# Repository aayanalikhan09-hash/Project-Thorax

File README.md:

# Project-Thorax
My first attempt at a custom PCB used to enable the detection of microplastics in different bodies of water tested across many different kinds of water.

This is a unique project state, so I will explain it.
Below is my ship comment that I feel explains the status well:

Hello everyone!
This is my magnum opus --- unfinished.
I hope to finish it soon and ship it to a different YSWS for funding, but for now it is just a concept in software.

I will still explain it, however.

This is meant to be a microplastic detection PCB that uses light spectroscopy to determine whether microplastics are present in water based on machine learning.

I wanted to make the PCB myself to learn the basics of electrical engineering and to also have some design freedom when it came to using specific components. The design was meant to use the very powerful ATSAMD series chip to coordinate many different concurrent processes, such as data transfer, flash memory storage, SD card storage, live ML model usage, Bluetooth data transfer, and data collection using the integrated sensor.

My data-collection plan is to set up a controlled lab environment with a single light source on the board, then take microplastic samples and place them in distilled water. After this, I will conduct hundreds of trials and collect data to see how the light response is received by the sensor. Each material's light response or reflected wavelength will allow the ML model to understand what constitutes a plastic/specifically red plastic, and what is not. The goal is to keep the project and its dependent variables as simple as possible so as not to overcomplicate data analysis and manipulation.

Post data collection, I plan to use the data to train a basic machine learning model on the patterns of how light is reflected on specific materials. This will allow for the distinction between specific material types and complete the project's overall goal of detecting microplastics in water. I intend to refine this later on with more funding and resources available to make this a reality and a golden standard to determine microplastic content in water.

For now, this is goodbye, everyone. It was fun seeing all of your amazing projects, and now you will see mine :)

See you guys soon!

Now that you have read through that, I must explain why a demo wasn't possible, what I'm doing in place of that, and how to get this thing running.

A demo was not possible because I've been bombarded with homework. If I had even had 75 percent of the homework I have right now, this project would likely be complete, amongst many other things. For reference, I'm taking 4 APs, two dual enrollments, organizing a haven(haven.hackclub.com/philly - GO CHECK IT OUT AHHH), youth group lead, library Teen Advisory Board president, and much more I'm probably forgetting. It's self-inflicted, so I have nobody to blame but myself, but that's an explanation, not an excuse.

What I'm doing is making the project files public, because that's literally all I have. I wish I could say I had more, but I don't. There is literally nothing else for me to give to all of you. I wish I could at least give the PCB, but then at that point I could ship, so it is what it is.

If you wanted to get this running, you can place TVS diodes on all the likely-to-be-exposed components and finish the PCB yourself in the PCB editor. A lot of the actual connections have all been done properly based on schematics; it just needs electrostatic discharge protection, so that's why I'm using TVS diodes. Technically, this is good to go right now, but you will absolutely static shock the components and fry them.

Until I figure out TVS diodes, I will be unable to properly ship this project. So I hope to figure that out soon and let you guys know how that goes!
I have attached a build notes document for your potential amusement; it's not all that exciting, but it does have some notes that I made for myself while making the PCB.
https://docs.google.com/document/d/10ZuE0ZeMz8bDbDXp7TKcbCHwWacSMxAw3u6ysEummEY/edit?usp=sharing

This is the end for now, but I will be back to finish this; I promise.

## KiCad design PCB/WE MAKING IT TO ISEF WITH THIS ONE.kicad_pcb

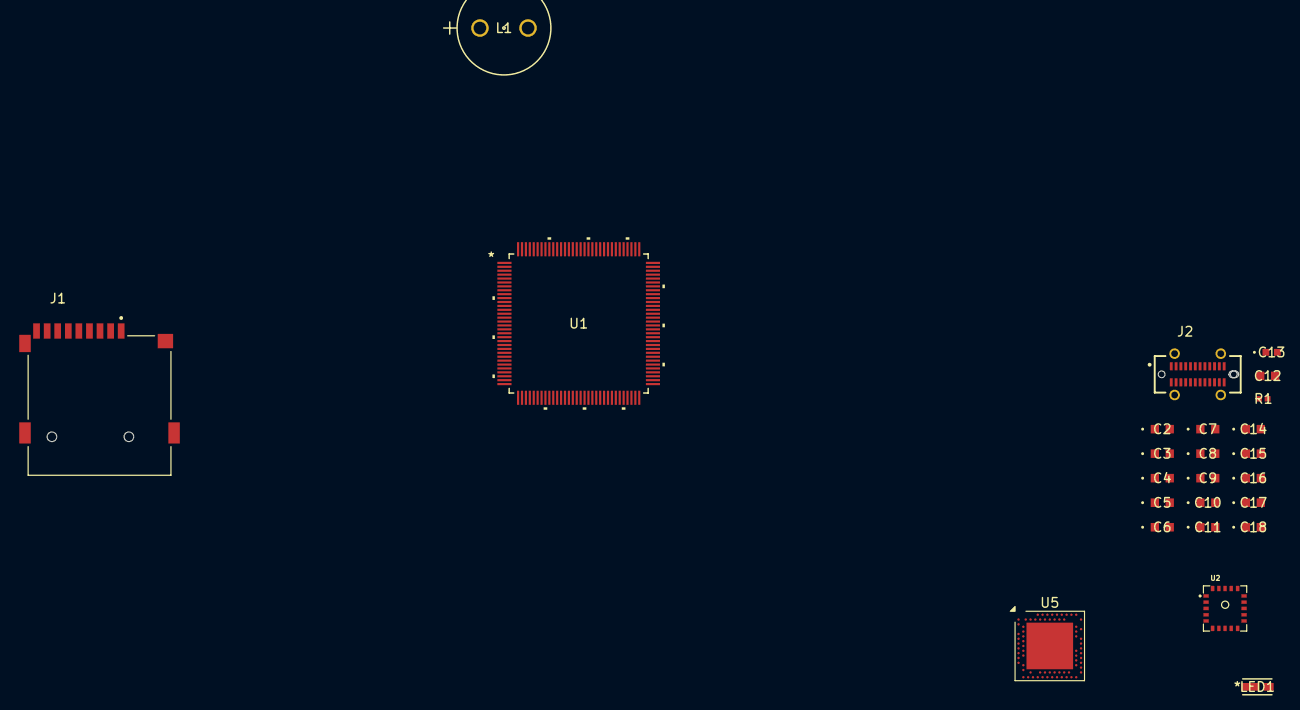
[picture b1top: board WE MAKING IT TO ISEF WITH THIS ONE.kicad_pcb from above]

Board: 2 copper layers, 25 parts (0 on the bottom side), 12 nets, no tracks yet.

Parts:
C2, C3, C4, C5, C6, C7, C8, C9, C10, C11, C14, C15, C16, C17, C18: C_US; CAP_GCM18_1p7X0p9X0p9_MUR
C12: C_US; CAP_GXT_1p7x0p9x0p9_MUR
C13: C_US; CAP_G_M1502_MUR
J1: MSD-1-A - SD Card Read; CUI_MSD-1-A
J2: USB_C_Receptacle; GCT_USB4225-03-1000-C_REVA
L1: L; 1300R_MUR
LED1: L130-5780HE1400001 - LED; LED_L130-5780HE1400001_PLL
R1: R; STA_RMCF0402_STP
U1: ATSAMD51P20A-AUT; TQFP128_14X14MC_MCH
U2: AS7263-BLGT - Spectrometer; PQFN065P470X450X260-20N
U5: nRF52833_QIxx; Nordic_AQFN-73-1EP_7x7mm_P0.5mm

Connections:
+3.3V: C2.1, C3.1, C4.1, C5.1, C6.1, C7.1, C8.1, C9.1, C10.1, C11.1, C15.1, C16.1, C17.1, R1.1, U1.6 (VDDANA), U1.15 (VDDANA), U1.26 (VDDANA), U1.32 (VDDIOB), U1.37 (VDDIOB), U1.46 (VDDIO), U1.54 (VDDIO), U1.65 (VDDIO), U1.79 (VDDIO), U1.91 (VDDIO), U1.97 (VDDIO), U1.107 (VDDIO), U1.118 (VDDIO)
GND: J1.G1 (COVER_GND), J1.G2 (COVER_GND__1), J1.G3 (COVER_GND__2), J1.G4 (COVER_GND__3)
GNDD: C2.2, C3.2, C4.2, C5.2, C6.2, C7.2, C8.2, C9.2, C10.2, C11.2, C12.2, C13.2, C14.2, C15.2, C16.2, C17.2, C18.2, U1.5 (GND), U1.14 (GNDANA), U1.25 (GNDANA), U1.31 (GND), U1.38 (GND), U1.45 (GND), U1.53 (GND), U1.64 (GND), U1.78 (GND), U1.90 (GND), U1.96 (GND), U1.106 (GND), U1.116 (GNDIO)
unnamed: J2.A1 (GND), J2.A12 (GND), J2.B1 (GND), J2.B12 (GND)
unnamed: J2.A4 (VBUS), J2.A9 (VBUS), J2.B4 (VBUS), J2.B9 (VBUS)
unnamed: C18.1, R1.2, U1.114 (RESETN)
unnamed: L1.2, U1.117 (VSW)
unnamed: C12.1, C13.1, C14.1, L1.1, U1.115 (VDDCORE)
unnamed: LED1.2, U2.15 (LED_DRV)
unnamed: U2.14 (VDD2), U2.17 (VDD1)
unnamed: U5.A22 (VDD), U5.AD14 (VDD), U5.AD23 (VDD), U5.B1 (VDD), U5.W1 (VDD)
unnamed: U5.B7 (VSS), U5.EP (VSS)

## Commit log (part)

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2026-06-15 try dos this time
2026-06-15 again
2026-06-15 ts is to make sure its consistent
2026-06-15 hack club maxxing
2026-06-15 last commit for now i think
2026-06-15 ig bro ig
2026-06-15 figure it out
